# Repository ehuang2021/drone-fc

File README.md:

# Custom nRF52832 Drone Flight Controller

The controller performs 500 Hz interrupt-driven IMU reads and atittude estimation, a 250 Hz PID control pipeline, drives ESC through hardware PWM, monitors a 2S LiPo battery through the ADC, and exposes system telementry and PID configurations over BLE, allowing for real-time PID tuning.
It's currently only for 1 axis, but will be scaled up for 3d space. 

## Key Structure/Features

### Firmware
- Zephyr RTOS with dedicated IMU, attitude-estimation, PID, PWM, safety, system-monitoring, and BLE threads
- GPIO interrupt and semaphore-driven MPU6050 acquisition at 500 Hz
- Non-blocking message queues between processing stages

### Attitude Estimation + Control
- Madgwick IMU filter using accelerometer and gyroscope data
- Quaternion-to-Euler conversion for roll, pitch, and yaw
- 250 Hz single-axis PID control loop
- ESC command generation through the nRF52 hardware PWM peripheral

### BLE Telemetry
- Custom BLE GATT service
- 20 Hz telemetry broadcasts with attitude, throttle, battery voltage, and uptime
- Writable BLE characteristic for runtime PID gain configuration

### System Monitoring
- ADC-based monitoring of a 2S LiPo battery through a voltage divider
- Moving-average voltage filtering
- Approximate battery SOC tracking
- Safety thread with heartbeat monitoring, roll-limit fault detection, and hardware watchdog support

## Architecture Overview
```mermaid
flowchart LR
    MPU["MPU6050<br/>500 Hz DRDY"] -->|GPIO interrupt| SEM["Semaphore"]
    SEM --> IMU["IMU Thread<br/>500 Hz<br/>I²C acquisition"]
    IMU -->|k_msgq| ATT["Attitude Thread<br/>500 Hz<br/>Madgwick Filter"]
    ATT -->|Downsample 2:1<br/>k_msgq| PID["PID Thread<br/>250 Hz"]
    PID -->|k_msgq| PWM["PWM Thread<br/>ESC command"]
    PWM --> ESC["ESC / Motor<br/>50 Hz PWM"]

    IMU -. heartbeat .-> SAFETY["Safety Thread<br/>watchdog / fault monitoring"]
    ATT -. heartbeat / roll .-> SAFETY
    PID -. heartbeat .-> SAFETY
    SAFETY -. flight state .-> PWM

    ATT -. attitude .-> BLE["BLE Telemetry Thread<br/>20 Hz notifications"]
    PID -. PID output .-> BLE
    PWM -. throttle .-> BLE

    ADC["2S LiPo<br/>ADC Monitor<br/>5 Hz"] -. voltage .-> BLE

    PHONE["nRF Connect / BLE Client"] -->|Write Kp, Ki, Kd| BLE
    BLE -->|PID command queue| PID
```

## Schematic
The custom PCB integrates the nRF52832 flight controller, MPU6050
interface, 2S LiPo voltage monitoring, ESC interface, 5 V-to-3.3 V
regulation, and SWD programming/debug access.

[View full schematic PDF](hardware/drone_fc_v1.0.pdf)

### PCB

## Future Additions:
- Three axis flight (which would probably mean a kalman filter over the current madgwick, with a gps module AND a nested PID loop)

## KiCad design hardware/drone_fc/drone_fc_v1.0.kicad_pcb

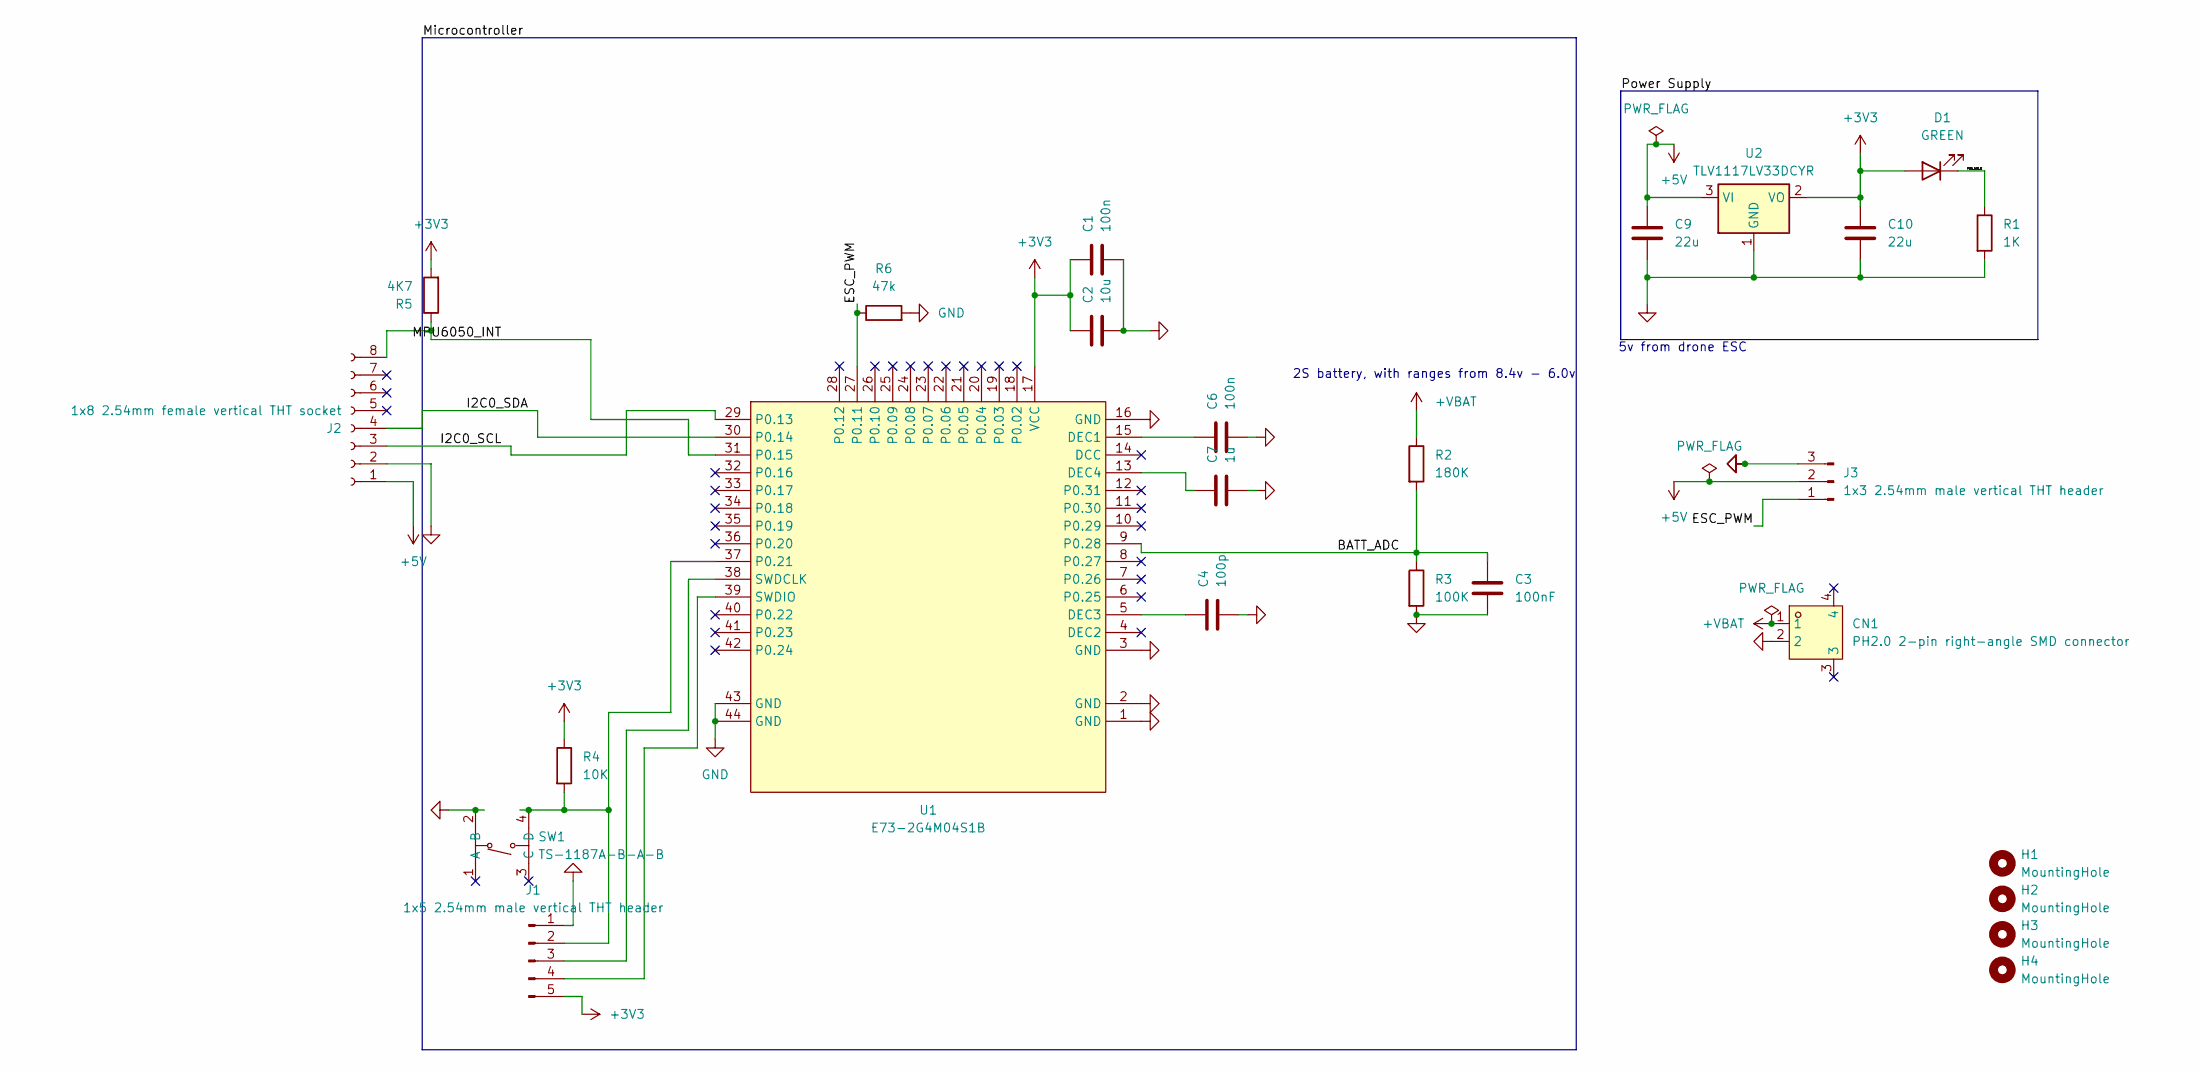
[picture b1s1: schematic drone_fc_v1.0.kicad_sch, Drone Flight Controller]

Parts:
C1, C6: 100n; C_0402_1005Metric; MPN CL05B104KB54PNC; LCSC Part C307331
C2: 10u; C_0603_1608Metric; MPN CL10A106KP8NNNC; LCSC Part C19702
C3: 100nF; C_0402_1005Metric; MPN CL05B104KB54PNC; LCSC Part C307331
C4: 100p; C_0402_1005Metric; MPN 0402CG101J500NT; LCSC Part C1546
C7: 1u; C_0402_1005Metric; MPN CL05A105KA5NQNC; LCSC Part C52923
C9, C10: 22u; C_0805_2012Metric; MPN C2012X5R1A226MT0J0E; LCSC Part C361180
CN1: PH2.0 2-pin right-angle SMD connector; CONN-SMD_PH2.0-1X2PW; MPN PH2.0-2P-LT; LCSC Part C722761
D1: GREEN; LED_0603_1608Metric; MPN SML-D13FWT86; LCSC Part C5372156
H1, H2, H3, H4: MountingHole; MountingHole_2.2mm_M2
J1: 1x5 2.54mm male vertical THT header; PinHeader_1x05_P2.54mm_Vertical; MPN CS-1109-1X5(L11.5)PA6T; LCSC Part C18213720
J2: 1x8 2.54mm female vertical THT socket; PinSocket_1x08_P2.54mm_Vertical; MPN 2.54-1*8P母环保; LCSC Part C27438
J3: 1x3 2.54mm male vertical THT header; PinHeader_1x03_P2.54mm_Vertical; MPN PZ2.54-1X3P-H25; LCSC Part C42431683
R1: 1K; R_0402_1005Metric; MPN 0402WGF1001TCE; LCSC Part C11702
R2: 180K; R_0402_1005Metric; MPN RC-02K1803FT; LCSC Part C324831
R3: 100K; R_0402_1005Metric; MPN 0402WGF1003TCE; LCSC Part C25741
R4: 10K; R_0402_1005Metric; MPN 0402WGF1002TCE; LCSC Part C25744
R5: 4K7; R_0402_1005Metric; MPN 0402WGF4701TCE; LCSC Part C25900
R6: 47k; R_0402_1005Metric
SW1: TS-1187A-B-A-B; SW-SMD_4P-L5.1-W5.1-P3.70-LS6.5-TL_H1.5; MPN TS-1187A-B-A-B; LCSC Part C318884
U1: E73-2G4M04S1B; WIRELM-SMD_E73-2G4M04S1B; MPN E73-2G4M04S1B; LCSC Part C411306
U2: TLV1117LV33DCYR; SOT-223-3_TabPin2; MPN TLV1117LV33DCYR; LCSC Part C15578

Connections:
+3V3: C1.1, C2.1, C10.1, D1.2 (A), J1.5, R4.1, R5.2, U1.17 (VCC), U2.2 (VO)
+5V: C9.1, J2.1, J3.2, U2.3 (VI)
+VBAT: CN1.1, R2.1
/BATT_ADC: C3.1, R2.2, R3.1, U1.9 (P0.28)
/ESC_PWM: J3.1, R6.1, U1.27 (P0.11)
/I2C0_SCL: J2.3, U1.29 (P0.13)
/I2C0_SDA: J2.4, U1.30 (P0.14)
/MPU6050_INT: J2.8, R5.1, U1.31 (P0.15)
/PWR_LED_K: D1.1 (K), R1.1
GND: C1.2, C2.2, C3.2, C4.2, C6.2, C7.2, C9.2, C10.2, CN1.2, J1.1, J2.2, J3.3, R1.2, R3.2, R6.2, SW1.2 (B), U1.1 (GND), U1.2 (GND), U1.3 (GND), U1.16 (GND), U1.43 (GND), U1.44 (GND), U2.1 (GND)
unnamed: J1.2, R4.2, SW1.4 (D), U1.37 (P0.21)
unnamed: J1.3, U1.38 (SWDCLK)
unnamed: J1.4, U1.39 (SWDIO)
unnamed: C6.1, U1.15 (DEC1)
unnamed: C4.1, U1.5 (DEC3)
unnamed: C7.1, U1.13 (DEC4)

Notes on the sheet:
2S battery, with ranges from 8.4v - 6.0v
5v from drone ESC

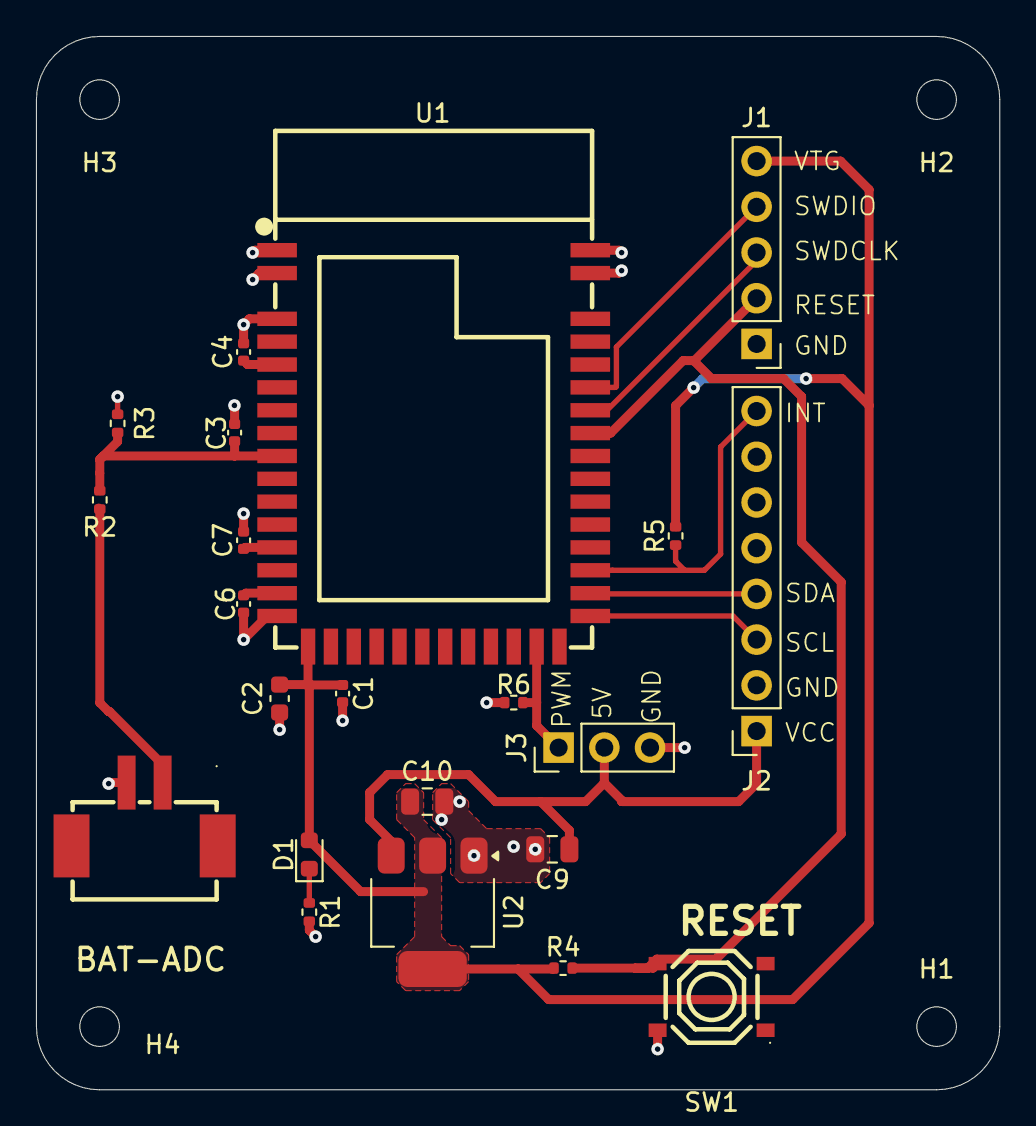
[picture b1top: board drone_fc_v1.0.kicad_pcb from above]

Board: 2 copper layers, 53.5 x 58.5 mm, 26 parts (0 on the bottom side), 16 nets.

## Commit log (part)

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2026-06-04 Initial commit for drone_fc
2026-06-04 Initial commit, mpu6050 driver
2026-06-04 changed code to outputting in csv
2026-06-04 fixed init_sensor logic with i2c passings
2026-06-04 added calibration during init and gyro setup
2026-06-07 Added initalize imu inturrupts
2026-06-07 renamed the imu struct variables since typing is too hard
2026-06-07 Added the semaphore and inturrupt logic, as well as all of the thread logic of passing data through minus the message queue
2026-06-07 Added GPIO port 11 and inturrupt support
2026-06-07 Linked imu.h
2026-06-07 added log
2026-06-08 Added the imu thread to main
2026-06-08 added inturrupt configurations for sensor
2026-06-08 Finished IMU thread, aongisde the message pipeline to the altitude thread
2026-06-08 added mpu_thread
2026-06-08 updates :D
2026-06-09 Refactored the filter to signal precision floats and replaced 64 bit double math to 32 bit to run on the nRF62832 FPU
2026-06-09 Added attiude and magdwick filter files
2026-06-09 First commit for the attitude thread, at first glance it works
2026-06-09 Changed the packet structure to the attitude thread to push float values for accel and gyro instead of uint16_t
2026-06-09 added attitude thread
2026-06-10 Started PCB layouts
2026-06-10 chore: stop tracking .DS_Store files
2026-06-10 chore: updated .gitignore to include KiCad files
2026-06-11 Fixed GYRO_LSB_SENS multiplier
2026-06-11 fix: SEq_n (Quanterion) values were changed to q->n values, now the filter no longer gets stuck
2026-06-11 update: changed debug messages from fixing madgwick filter. This thread should be working now.
2026-06-11 feat: initial schematic design
    Completed the base schematic for the project. Major hardware blocks include:
    - nRF52832 core setup (configured for internal LDO, 32MHz crystal only)
    - 5V to 3.3V linear regulator for ESC power input
    - 2S battery voltage divider (180k/100k) mapped to AIN
    - MPU6050 IMU on I2C0 with active-low interrupt and external pull-up
    - Hardware reset button with 10k pull-up resistor
2026-06-11 Added .vscode
2026-06-12 feat: Finished schematics, and most of the footprinting
